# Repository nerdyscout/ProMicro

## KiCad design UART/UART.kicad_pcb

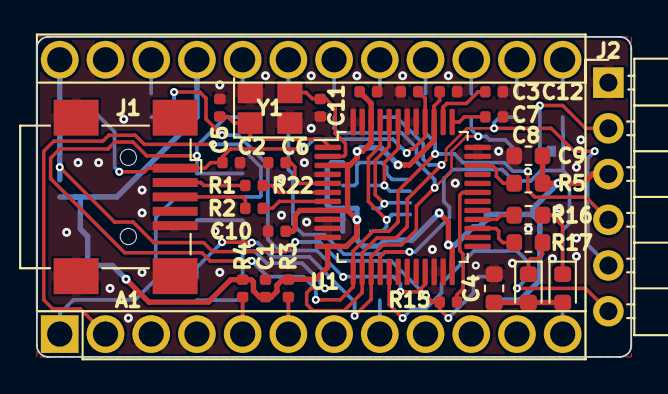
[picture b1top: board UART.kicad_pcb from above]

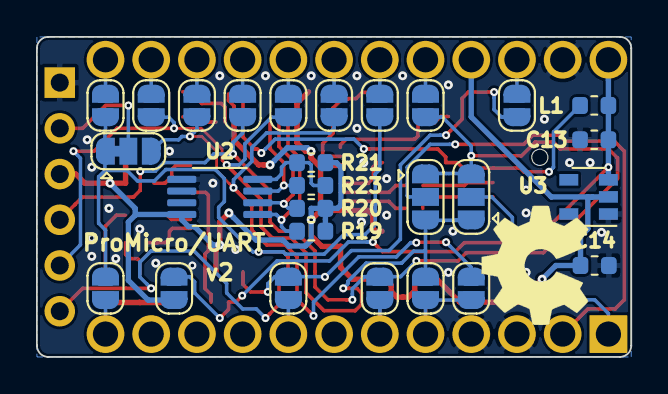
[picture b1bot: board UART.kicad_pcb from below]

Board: 4 copper layers, 33.0 x 17.8 mm, 56 parts (28 on the bottom side), 45 nets.

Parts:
A1: Sparkfun_Pro_Micro_3V3; Sparkfun_Pro_Micro
C1, C3, C7, C8, C10, C11, C12: 100n; C_0402_1005Metric
C2: 4.7µ; C_0402_1005Metric
C4: 10µ; C_0603_1608Metric
C5, C6: 27p; C_0402_1005Metric
C9: 4.7µ; R_0603_1608Metric
C13, C14: 1µ; C_0603_1608Metric
D1: TX; LED_0603_1608Metric
D2: RX; LED_0603_1608Metric
J1: USB_B_Mini; USB_Mini-B_Wuerth_65100516121_Horizontal
J2: Conn_01x06; PinHeader_1x06_P2.54mm_Horizontal
JP1, JP2, JP3, JP4, JP5, JP6, JP7, JP8, JP9, JP12, JP13, JP14, JP15, JP17, JP18: Jumper_NO_Small; SolderJumper-2_P1.3mm_Open_RoundedPad1.0x1.5mm
JP10, JP11: Jumper_3_Bridged12; SolderJumper-3_P1.3mm_Open_RoundedPad1.0x1.5mm
JP16: Jumper_3_Bridged12; SolderJumper-3_P1.3mm_Bridged12_RoundedPad1.0x1.5mm
L1: 0; L_0603_1608Metric
LOGO1: Logo_Open_Hardware_Small; OSHW-Symbol_6.7x6mm_SilkScreen
R1, R2: 22; R_0402_1005Metric
R3, R4: 4k7; R_0402_1005Metric
R5: 1k; R_0603_1608Metric
R15: 39k; R_0402_1005Metric
R16, R17: 220; R_0603_1608Metric
R19, R20, R21: 10k; R_0603_1608Metric
R22: 12k; R_0402_1005Metric
R23: 2k; R_0603_1608Metric
U1: FT232H; LQFP-48_7x7mm_P0.5mm
U2: 93CxxB; MSOP-8_3x3mm_P0.65mm
U3: AZ1117-3.3; SOT-23-5
Y1: 12MHz; Crystal_SMD_3225-4Pin_3.2x2.5mm

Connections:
+3V3: A1.21, C1.1, C4.1, C9.1, C10.2, C11.2, C12.1, C14.1, D1.2, D2.2, J2.3, JP18.2, R3.2, R4.2, R5.2, R19.2, R20.2, R21.2, U1.3, U1.8, U1.12, U1.24, U1.39, U1.46, U2.8, U3.2
+5V: A1.24, C13.1, JP18.1, L1.1, R15.2, U3.3
/CIPO: A1.15, JP3.2
/COPI: A1.14, JP2.2
/CS0: A1.13, JP5.2
/CS1: A1.12, JP4.2
/EECLK: R20.1, U1.44, U2.2
/EECS: R19.1, U1.45, U2.1
/EEDAT: R23.1, U1.43, U2.3
/PWM: A1.8, JP12.2
/RXD: A1.1, JP10.2
/SCK: A1.16, JP1.2
/SCL: A1.6, JP15.2, R3.1
/SDA: A1.5, JP13.2, JP14.2, R4.1
/TCK: A1.20, JP6.2
/TDI: A1.17, JP7.2
/TDO: A1.18, JP8.2
/TMS: A1.19, JP9.2
/TXD: A1.2, JP11.2
/~RST: A1.22, JP17.2
ACBUS0: JP12.1, JP17.1, U1.21
ADBUS0: J2.4, JP1.1, JP6.1, JP10.3, JP11.1, JP15.1, U1.13
ADBUS1: J2.5, JP2.1, JP7.1, JP10.1, JP11.3, JP13.1, U1.14
ADBUS2: JP3.1, JP8.1, JP14.1, JP16.3, U1.15
ADBUS3: JP4.1, JP5.1, JP9.1, JP16.1, U1.16
ADBUS4: J2.6, U1.17
GND: A1.3, A1.4, A1.23, C1.2, C2.2, C3.2, C4.2, C5.2, C6.2, C7.2, C8.2, C9.2, C10.1, C11.1, C12.2, C13.2, C14.2, J1.5, J1.6, J2.1, R22.2, U1.4, U1.9, U1.10, U1.11, U1.22, U1.23, U1.35, U1.36, U1.41, U1.42, U1.47, U1.48, U2.5, U3.1, Y1.2, Y1.4
unnamed: C2.1, C3.1, J1.1, L1.2, U1.40
unnamed: C5.1, U1.1, Y1.1
unnamed: C6.1, U1.2, Y1.3
unnamed: C7.1, U1.38
unnamed: C8.1, U1.37
unnamed: D1.1, R16.2
unnamed: D2.1, R17.2
unnamed: J1.2, R1.2
unnamed: J1.3, R2.2
unnamed: J2.2, JP16.2
unnamed: R1.1, U1.6
unnamed: R2.1, U1.7
unnamed: R5.1, U1.34
unnamed: R21.1, R23.2, U2.4
unnamed: R22.1, U1.5
PWRSAV: R15.1, U1.31
RXLED: R17.1, U1.27
TXLED: R16.1, U1.28

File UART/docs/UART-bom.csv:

References;Description;Part;Value;Qty;lcsc#;mpn
A1;;Sparkfun_Pro_Micro;Sparkfun_Pro_Micro_3V3;1;;
C5 C6;Unpolarized capacitor;C;27p;2;C19702;0402CG270J500NTN
C1 C3 C7 C8 C10 C11 C12;Unpolarized capacitor;C;100n;7;C1525;CL05B104KO5NNNC
C13 C14;Unpolarized capacitor;C;1µ;2;C15849;CL10A105KB8NNNC
C2;Unpolarized capacitor;C;4.7µ;1;C23733;CL05A475MP5NRNC
C9;Unpolarized capacitor;C;4.7µ;1;C19666;CL10A475KO8NNNC
C4;Unpolarized capacitor;C;10µ;1;C15525;CL10A106KP8NNNC
D2;Light emitting diode;LED;RX;1;C72043;19-217/GHC-YR1S2/3T
D1;Light emitting diode;LED;TX;1;C72043;19-217/GHC-YR1S2/3T
J2;Generic connector, single row, 01x06, script generated (kicad-library-utils/schlib/autogen/connector/);Conn_01x06;Conn_01x06;1;;
J1;USB Mini Type B connector;USB_B_Mini;USB_B_Mini;1;;
L1;Inductor, small symbol;L_Small;0;1;;
R1 R2;Resistor;R;22;2;C25092;0402WGF220JTCE
R16 R17;Resistor;R;220;2;C22962;0603WAF2200T5E
R5;Resistor;R;1k;1;C21190;0603WAF1001T5E
R23;Resistor;R;2k;1;C22975;0603WAF2001T5E
R3 R4;Resistor;R;4k7;2;C25900;0402WGF4701TCE
R19 R20 R21;Resistor;R;10k;3;C25804;0603WAF1002T5E
R22;Resistor;R;12k;1;C25752;0402WGF1202TCE
R15;Resistor;R;39k;1;C25783;0402WGF3902TCE
U2;Serial EEPROM, 93 Series, 5.0V, DIP-8/SOIC-8;93CxxB;93CxxB;1;;
U3;1A 20V Fixed LDO Linear Regulator, 3.3V, SOT-89/SOT-223/TO-220/TO-252/TO-263;AZ1117-3.3;AZ1117-3.3;1;;
U1;Hi Speed Single Channel USB UART/FIFO, LQFP/QFN-48;FT232H;FT232H;1;C51997;FT232HL
Y1;Four pin crystal, GND on pins 2 and 4, small symbol;Crystal_GND24_Small;12MHz;1;;

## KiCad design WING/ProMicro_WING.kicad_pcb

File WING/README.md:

# ProMicro_WING

## Documentation 
All files can be found on [Github](https://github.com/nerdyscout/ProMicro/tree/master/WING).

### Schematic

### BoM
  * [interactiveHTMLBoM](https://nerdyscout.github.io/ProMicro/WING/docs/bom/WING-ibom.html)
  * [octopart](docs/bom/WING-bom_octopart.csv)

## Hardware 
### Layout

### Gerbers
can be found within the Github [repository](gerbers).

## external
### Links
  * [hackaday.io](https://hackaday.io/project/171898-promicro)

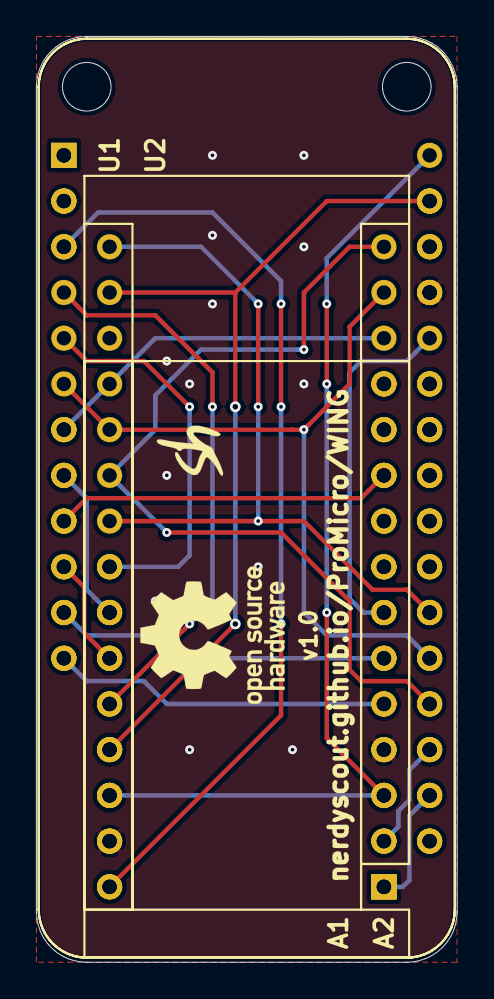
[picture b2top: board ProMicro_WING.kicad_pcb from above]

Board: 2 copper layers, 23.4 x 51.4 mm, 8 parts (0 on the bottom side), 19 nets.

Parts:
A1: Sparkfun_Pro_Micro_3V3; Sparkfun_Pro_Micro
A2: Arduino_Nano_v3.x; Arduino_Nano_mod
LOGO1: Logo_Open_Hardware_Small; OSHW-Logo_7.5x8mm_SilkScreen
TP1, TP2: TestPoint; MountingHole_2.7mm
TP3: initials
U1: Adafruit_HUZZAH32_ESP32_Feather; Adafruit_Feather_mod2
U2: Adafruit_Feather_HUZZAH_ESP8266; Adafruit_Feather

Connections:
+3V3: A1.21, A2.17, A2.27, U1.27, U2.27
+5V: A1.24, U1.3, U2.3
A0: A1.17, U1.5
A1: A1.18, U1.8, U2.8
A2: A1.19, U1.10, U2.10
A3: A1.20, U1.4
D0: A1.2, U1.15, U2.15
D1: A1.1, U1.14, U2.14
D2: A1.5, U1.12, U2.12
D3: A1.6, U1.11, U2.11
D4: A1.7, U2.24
D7: A1.10, U1.9, U2.9
D10: A1.13, U1.7, U2.7
D14: A1.15, U1.16, U2.16
D15: A1.16, U1.18, U2.18
D16: A1.14, U1.6, U1.17, U2.17
EN: U1.2, U2.2
GND: A1.4, A1.23, A2.4, A2.29, U1.25, U2.25
Reset: A1.3, A1.22, A2.3, A2.28, U2.28

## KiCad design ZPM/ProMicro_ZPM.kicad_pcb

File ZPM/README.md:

# ProMicro_ZPM 
This module can be mounted to an [Arduino Pro Mini](https://www.sparkfun.com/products/11113), [Arduino Nano](https://store.arduino.cc/arduino-nano), [Sparkfun Pro Micro](https://www.sparkfun.com/products/12587), or any other pincompatible MCU running with 3.3V.

## Documentation
All files can be found on [Github](https://github.com/nerdyscout/ProMicro/tree/master/ZPM).

### Schematic

### BoM
  * [interactiveHTMLBoM](https://nerdyscout.github.io/ProMicro/ZPM/docs/bom/ZPM-ibom.html)
  * [octopart](docs/bom/ZPM-bom_octopart.csv)

## Hardware 
### Layout

## Gerbers
can be found within the Github [repository](gerbers).

## external
### Links
  * [hackaday.io](https://hackaday.io/project/171898-promicro)

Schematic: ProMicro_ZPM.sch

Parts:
A1: Sparkfun_Pro_Micro_3V3; Sparkfun_Pro_Micro
C1: 10µF; CP_Elec_4x3
C2: 1µ; C_0603_1608Metric
C3, C4: 4.7µ; C_0603_1608Metric
J1: Screw_Terminal_01x05; TerminalBlock_TE_282834-5_1x05_P2.54mm_Horizontal
J3: JST; JST_PH_S2B-PH-SM4-TB_1x02-1MP_P2.00mm_Horizontal
JP2, JP3: SolderJumper_3_Bridged12; SolderJumper-3_P1.3mm_Bridged12_RoundedPad1.0x1.5mm
JP4: SolderJumper_2_Open; SolderJumper-2_P1.3mm_Open_RoundedPad1.0x1.5mm
L1: CDRH2D18_HPNP-100C; HPNP-100NC
LOGO1: Logo_Open_Hardware_Small; OSHW-Symbol_6.7x6mm_SilkScreen
Q1: BC847; SOT-23
R1: 2k; R_0603_1608Metric
TP1: TestPoint; TestPoint_Pad_D2.5mm
U1: LTC3588EDD-1PBF; MSOP-10-1EP_3x3mm_P0.5mm_EP1.68x1.88mm_ThermalVias
U2: MCP73831-2-OT; SOT-23-5

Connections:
+3V3: A1.21, C1.1, J1.3, L1.1, U1.6
/D0: JP2.2 (C), U1.9
/D1: JP3.2 (C), U1.8
/Vin2: C4.1, JP2.3 (B), JP3.1 (A), U1.7
GND: A1.4, A1.23, C1.2, C3.2, C4.2, J1.1, J3.1, JP2.1 (A), JP3.3 (B), Q1.2 (E), R1.2, U1.11, U2.2 (VSS)
unnamed: C2.1, U1.3
unnamed: J1.4, U1.2
unnamed: J1.5, U1.1
unnamed: JP4.2 (B), Q1.1 (B), U1.10
unnamed: L1.2, U1.5
unnamed: R1.1, U2.5 (PROG)
Reset: A1.22, JP4.1 (A), Q1.3 (C)
VBAT: C2.2, C3.1, J1.2, J3.2, TP1.1, U1.4, U2.3 (VBAT)
VCC: A1.24, U2.4 (VDD)

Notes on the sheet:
default Vout = 3.3V

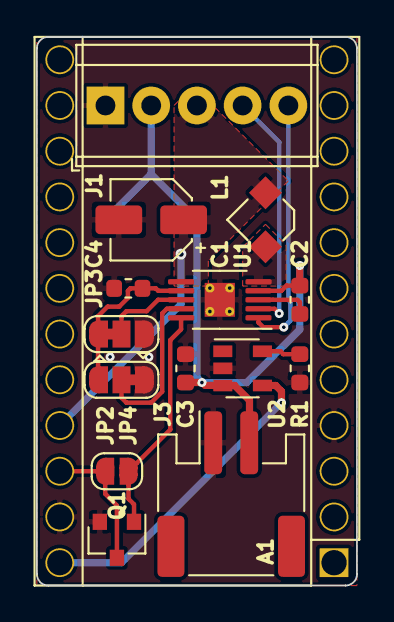
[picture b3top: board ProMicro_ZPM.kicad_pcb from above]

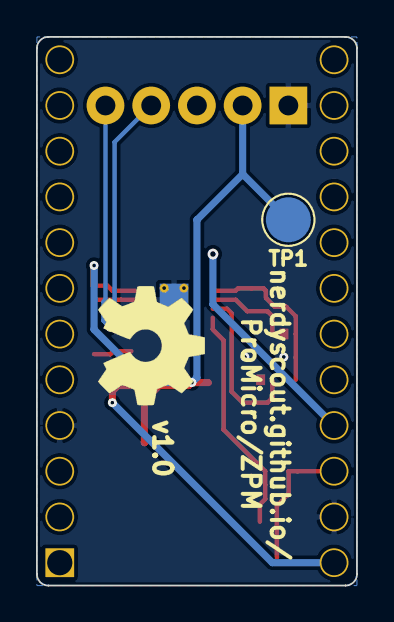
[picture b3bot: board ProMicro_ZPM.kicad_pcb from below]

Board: 2 copper layers, 17.8 x 30.5 mm, 17 parts (2 on the bottom side), 14 nets.

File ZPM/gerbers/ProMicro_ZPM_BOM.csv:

Component;Description;Part;References;Value;Footprint;Quantity Per PCB;Datasheet
1;Unpolarized capacitor;C;C2;1µ;C_0603_1608Metric;1;~
2;Unpolarized capacitor;C;C3 C4;4.7µ;C_0603_1608Metric;2;~
3;Polarized capacitor;CP;C1;10µF;CP_Elec_4x3;1;~
4;Generic connector, single row, 01x02, script generated (kicad-library-utils/schlib/autogen/connector/);Conn_01x02;J3;JST;JST_PH_S2B-PH-SM4-TB_1x02-1MP_P2.00mm_Horizontal;1;~
5;Generic screw terminal, single row, 01x05, script generated (kicad-library-utils/schlib/autogen/connector/);Screw_Terminal_01x05;J1;Screw_Terminal_01x05;TerminalBlock_TE_282834-5_1x05_P2.54mm_Horizontal;1;~
6;0.1A Ic, 45V Vce, NPN Transistor, SOT-23;BC847;Q1;BC847;SOT-23;1;http://www.infineon.com/dgdl/Infineon-BC847SERIES_BC848SERIE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
7;Resistor;R;R1;2k;R_0603_1608Metric;1;~
8;Single cell, Li-Ion/Li-Po charge management controller, 4.20V, Tri-State Status Output, in SOT23-5 package;MCP73831-2-OT;U2;MCP73831-2-OT;SOT-23-5;1;http://ww1.microchip.com/downloads/en/DeviceDoc/20001984g.pdf

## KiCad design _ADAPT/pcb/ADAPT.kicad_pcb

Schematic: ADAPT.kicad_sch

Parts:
A1: Arduino_UNO_R3
A2, A4, A5: Sparkfun_Pro_Micro; ProMicro
A3: Adafruit_Feather_Generic; Adafruit_Feather
J1, J2, J3: VBAT; PinHeader_1x01_P2.54mm_Vertical
J4, J5: Conn_01x02; PinHeader_1x02_P2.54mm_Vertical
JP1, JP2, JP4, JP6: SolderJumper_2_Open; SolderJumper-2_P1.3mm_Open_RoundedPad1.0x1.5mm
JP3, JP5: SolderJumper_3_Open; SolderJumper-3_P1.3mm_Open_RoundedPad1.0x1.5mm
LOGO1: Logo_Open_Hardware_Small; OSHW-Symbol_6.7x6mm_SilkScreen

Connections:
+3V3: A1.4 (3V3), A2.21, A3.2 (3V3), A4.21, A5.21, JP3.1 (A)
+5V: A1.5 (+5V), A2.24, A3.26 (USB), A4.24, A5.24
A0: A1.9 (A0), A2.17, A3.5 (A0), A4.17, A5.17, JP5.2 (C)
A1: A1.10 (A1), A2.18, A3.6 (A1), A4.18, A5.18
A2: A1.11 (A2), A2.19, A3.7 (A2), A4.19, A5.19
A3: A1.12 (A3), A2.20, A3.8 (A3), A4.20, A5.20
AREF: A1.30 (AREF), A3.3 (AREF)
BTN: A2.9, A4.9, A5.9, JP5.3 (B)
CIPO: A1.27 (D12), A2.15, A3.13 (MISO), A4.15, A5.15
COPI: A1.26 (D11), A2.14, A3.12 (MOSI), A4.14, A5.14
CS0: A1.25 (D10), A2.13, A3.22 (D3), A4.13, A5.13
CS1: A1.24 (D9), A2.12, A3.23 (D4), A4.12, A5.12
D8: A1.23 (D8), A2.11, A3.25 (D6), A4.11, A5.11
GND: A1.6 (GND), A1.7 (GND), A1.29 (GND), A2.3, A2.4, A2.23, A3.4 (GND), A4.3, A4.4, A4.23, A5.3, A5.4, A5.23, JP3.3 (B)
INT: A1.17 (D2), A2.10, A3.21 (D2), A4.10, A5.10
unnamed: A3.9 (A4), JP6.1 (A)
unnamed: A3.10 (A5), JP4.1 (A)
unnamed: A3.19 (D0), JP1.2 (B)
unnamed: A3.20 (D1), JP2.2 (B)
unnamed: J1.1, J2.1, J3.1
PWM: A1.20 (D5), A2.8, A3.24 (D5), A4.8, A5.8
RXD: A1.16 (D1/TX), A2.1, A3.14 (RX), A4.1, A5.1, JP1.1 (A)
SCK: A1.28 (D13), A2.16, A3.11 (SCK), A4.16, A5.16
SCL: A1.13 (SDA/A4), A1.32 (SCL/A5), A2.6, A3.18 (SCL), A4.6, A5.6, J4.2, J5.2, JP6.2 (B)
SDA: A1.14 (SCL/A5), A1.31 (SDA/A4), A2.5, A3.17 (SDA), A4.5, A5.5, J4.1, J5.1, JP4.2 (B)
SPARE: A3.16 (SPARE), JP3.2 (C)
STAT: A1.19 (D4), A2.7, A4.7, A5.7, JP5.1 (A)
TXD: A1.15 (D0/RX), A2.2, A3.15 (TX), A4.2, A5.2, JP2.1 (A)
~RST: A1.3 (~RESET), A2.22, A3.1 (~RESET), A4.22, A5.22

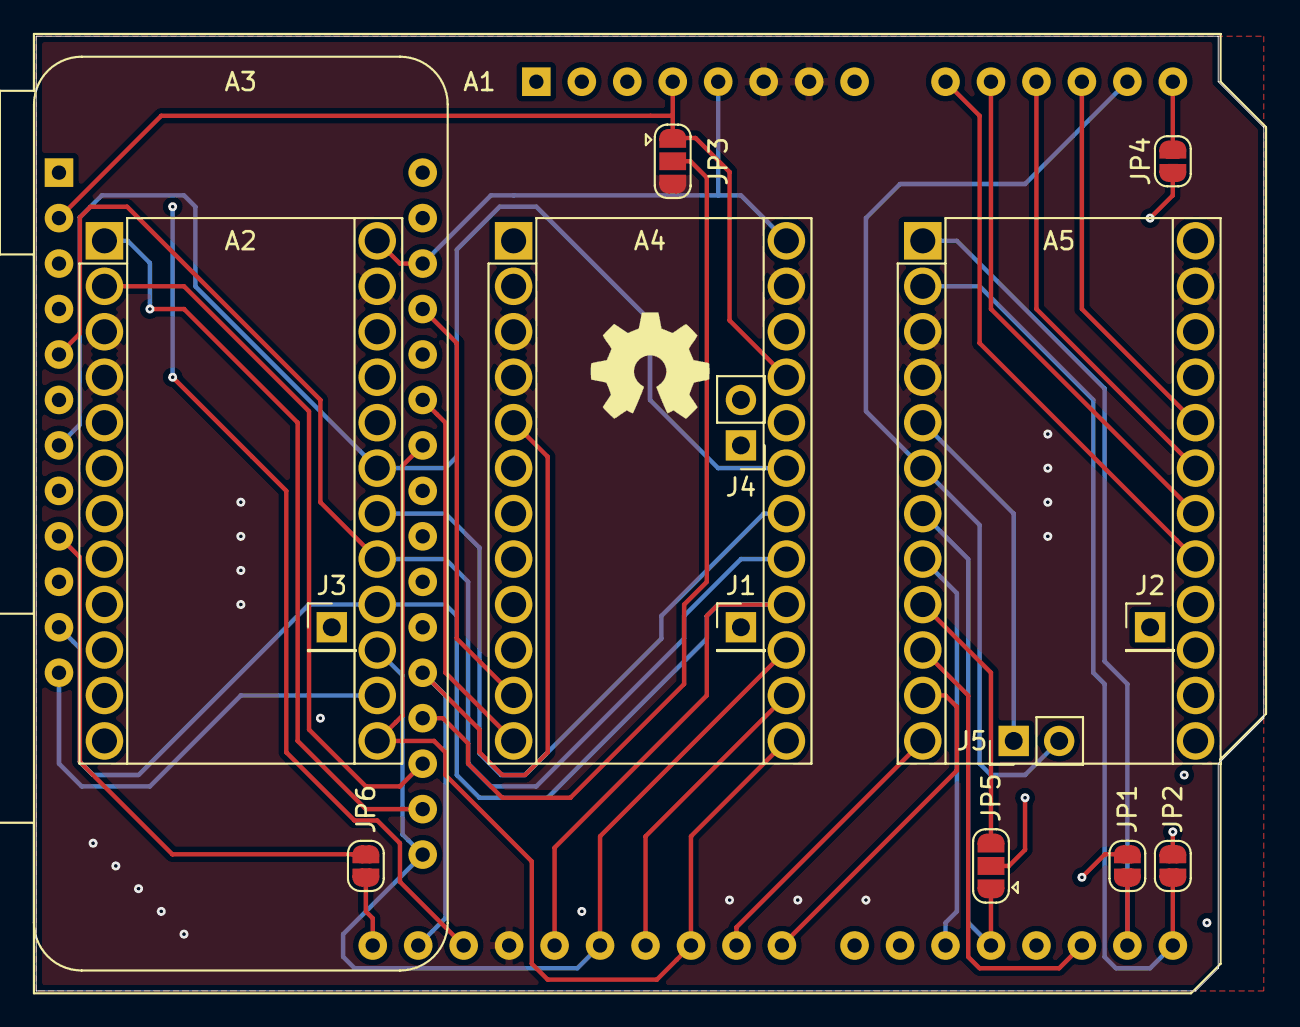
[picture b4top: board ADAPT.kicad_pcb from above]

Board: 4 copper layers, 68.6 x 53.3 mm, 17 parts (0 on the bottom side), 29 nets.

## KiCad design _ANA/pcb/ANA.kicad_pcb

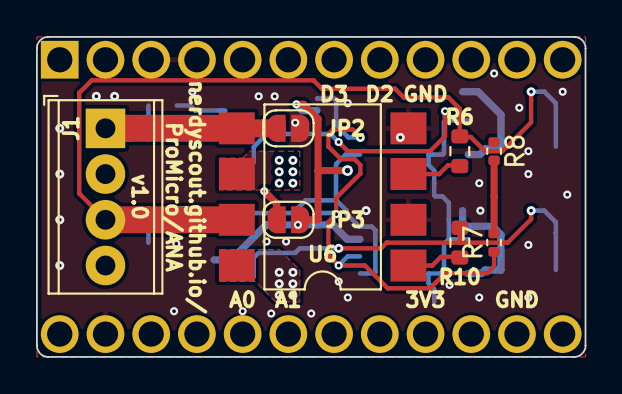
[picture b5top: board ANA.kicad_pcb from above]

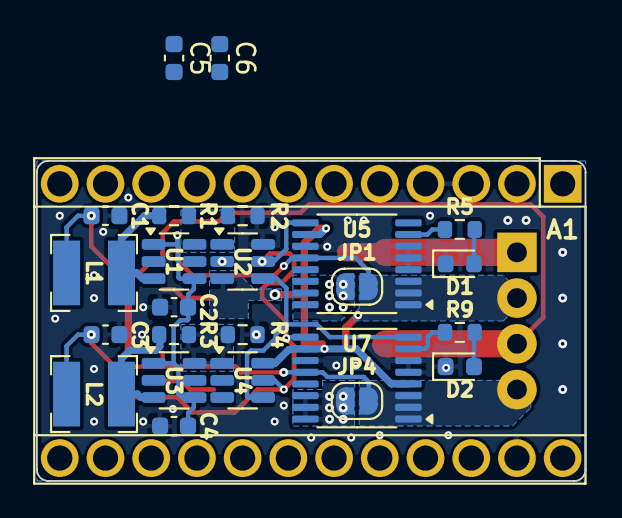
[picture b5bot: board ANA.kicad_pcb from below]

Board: 2 copper layers, 30.5 x 17.8 mm, 34 parts (25 on the bottom side), 20 nets.

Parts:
A1: Sparkfun_Pro_Micro
C1, C3: 10µ; C_0603_1608Metric
C2, C4: 4.7µ; C_0603_1608Metric
C5, C6: 100n; C_0603_1608Metric
D1, D2: LED; LED_0603_1608Metric
J1: Conn_01x04; TerminalBlock_Phoenix_MPT-0,5-4-2.54_1x04_P2.54mm_Horizontal
JP1, JP2, JP3, JP4: Jumper_NO_Small; SolderJumper-2_P1.3mm_Open_RoundedPad1.0x1.5mm
L1, L2: 2.2µ; L_Bourns-SRN4018
LOGO1: Logo_Open_Hardware_Small; OSHW-Symbol_6.7x6mm_SilkScreen
R1, R3: 200k; R_0603_1608Metric
R2, R4: 47k; R_0603_1608Metric
R5, R6, R9, R10: 220; R_0603_1608Metric
R7, R8: 4k7; R_0402_1005Metric
U1, U3: TLV62569DDC; SOT-23-6
U2, U4: MCP4725xxx-xCH; SOT-23-6
U5, U7: INA260; TSSOP-16_4.4x5mm_P0.65mm
U6: LTV-827S; SMDIP-8_W9.53mm

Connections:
+3V3: A1.21, C5.1, C6.1, JP3.2, R7.2, R8.2, U2.3, U4.3, U4.6, U5.10, U7.4, U7.10
A0: A1.17, C1.1, J1.3, L1.1, R6.2, U6.5
A1: A1.18, C3.1, J1.4, JP4.1, L2.1, R10.2, U7.1, U7.2, U7.3, U7.12
GND: A1.3, A1.4, A1.23, C1.2, C2.2, C3.2, C4.2, C5.2, C6.2, D1.1, D2.1, JP2.2, R2.1, R4.1, U1.2, U2.2, U2.6, U3.2, U4.2, U5.4, U5.5, U5.6, U5.11, U6.2, U6.4, U7.5, U7.6, U7.11
unnamed: C2.1, C4.1, J1.2, JP1.1, JP3.1, U1.1, U1.4, U3.1, U3.4, U5.1, U5.2, U5.3, U5.12
unnamed: D1.2, R5.1
unnamed: D2.2, R9.1
unnamed: J1.1, JP2.1, U6.7
unnamed: JP1.2, U5.14, U5.15, U5.16, U6.8
unnamed: JP4.2, U6.6, U7.14, U7.15, U7.16
unnamed: L1.2, R1.2, U1.3
unnamed: L2.2, R3.2, U3.3
unnamed: R1.1, R2.2, U1.6, U2.1
unnamed: R3.1, R4.2, U3.6, U4.1
unnamed: R5.2, U5.7
unnamed: R6.1, U6.1
unnamed: R9.2, U7.7
unnamed: R10.1, U6.3
SCL: A1.6, R7.1, U2.5, U4.5, U5.9, U7.9
SDA: A1.5, R8.1, U2.4, U4.4, U5.8, U7.8

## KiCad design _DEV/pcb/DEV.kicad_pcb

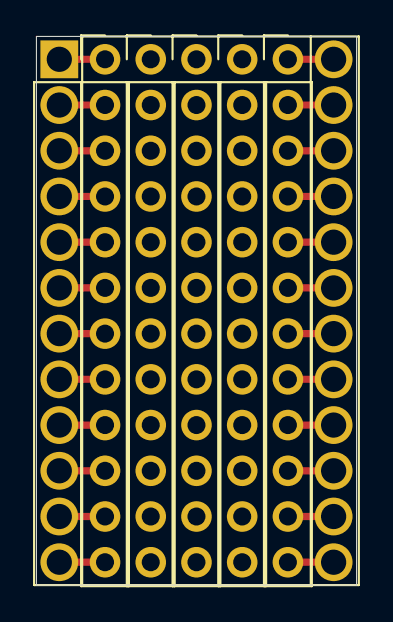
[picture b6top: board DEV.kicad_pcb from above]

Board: 2 copper layers, 17.8 x 30.5 mm, 6 parts (0 on the bottom side), 22 nets.

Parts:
A1: Sparkfun_Pro_Micro; ProMicro
J1, J2, J3, J4, J5: Conn_01x12; PinHeader_1x12_P2.54mm_Vertical

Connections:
+3V3: A1.21, J2.4
+5V: A1.24, J2.1
BTN: A1.9, J1.9
CIPO: A1.15, J2.10
COPI: A1.14, J2.11
CS0: A1.13, J2.12
CS1: A1.12, J1.12
D8: A1.11, J1.11
GND: A1.3, A1.4, A1.23, J1.3, J1.4, J2.2
INT: A1.10, J1.10
PWM: A1.8, J1.8
RXD: A1.1, J1.1
SCK: A1.16, J2.9
SCL: A1.6, J1.6
SDA: A1.5, J1.5
STAT: A1.7, J1.7
TCK: A1.20, J2.5
TDI: A1.17, J2.8
TDO: A1.18, J2.7
TMS: A1.19, J2.6
TXD: A1.2, J1.2
~RST: A1.22, J2.3

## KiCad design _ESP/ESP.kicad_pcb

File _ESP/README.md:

# ProMicro_ESP 
This module can be mounted to an [Arduino Pro Mini](https://www.sparkfun.com/products/11113), [Arduino Nano](https://store.arduino.cc/arduino-nano), [Sparkfun Pro Micro](https://www.sparkfun.com/products/12587), or any other pincompatible MCU running with 3.3V.

## Documentation 
All files can be found on [Github](https://github.com/nerdyscout/ProMicro/tree/master/ESP).

### Schematic

### BoM
  * [interactiveHTMLBoM](https://nerdyscout.github.io/ProMicro/ESP/docs/bom/ESP-ibom.html)
  * [octopart](pcb/docs/bom/ESP-bom_octopart.csv)

## Hardware 
### Layout

### Gerbers
can be found within the Github [repository](pcb/gerbers).

## Code  (unless otherwise stated)
 * [blink](examples/blink/blink.ino)

## external
### Links
  * [hackaday.io](https://hackaday.io/project/171898-promicro)

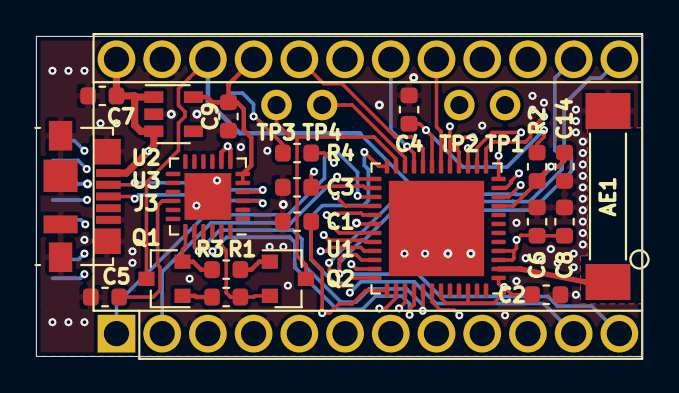
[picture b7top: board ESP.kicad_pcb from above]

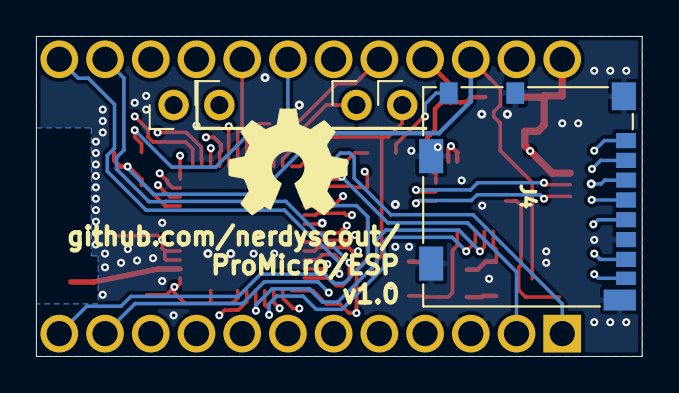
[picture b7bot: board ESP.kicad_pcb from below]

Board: 4 copper layers, 33.7 x 17.8 mm, 28 parts (6 on the bottom side), 44 nets.

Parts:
A1: Sparkfun_Pro_Micro; ProMicro
AE1: Antenna_Chip; SMD_ANT9520
C1, C2, C7, C14: 1µ; C_0603_1608Metric
C3, C9: 0.1n; C_0603_1608Metric
C4, C6: 100n; C_0603_1608Metric
C5: DNP; C_0603_1608Metric
C8: 10n; C_0603_1608Metric
J3: USB_B_Micro; USB_Micro-B_Molex_47346-0001
J4: Micro_SD_Card_Det; microSD_HC_Molex_104031-0811
LOGO1: Logo_Open_Hardware_Small; OSHW-Symbol_6.7x6mm_SilkScreen
Q1, Q2: mmbt2222; SOT-23
R1, R2, R3, R4: 10k; R_0603_1608Metric
TP1: GPIO21; PinHeader_1x01_P2.54mm_Vertical
TP2: GPIO22; PinHeader_1x01_P2.54mm_Vertical
TP3: GPIO0; PinHeader_1x01_P2.54mm_Vertical
TP4: GPIO2; PinHeader_1x01_P2.54mm_Vertical
U1: ESP32-PICO-D4; QFN-48-1EP_7x7mm_P0.5mm_EP5.3x5.3mm
U2: AP2112K-3.3; SOT-23-5
U3: CP2104; QFN-24-1EP_4x4mm_P0.5mm_EP2.6x2.6mm

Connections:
+3V3: A1.21, C1.1, C2.1, C4.1, C6.1, C8.1, C9.1, R2.1, U1.1, U1.3, U1.4, U1.19, U1.37, U1.43, U1.46, U2.5, U3.5, U3.6
+5V: A1.24, C7.1, J3.1, U2.1, U2.3, U3.7, U3.8
/CLK: J4.5, U1.31
/CMD: J4.3, U1.30
/D0: J4.7, U1.32
/D1: J4.8, U1.33
/D2: J4.1, U1.28
/D3: J4.2, U1.29
/D+: J3.3, U3.3
/D-: J3.2, U3.4
/DTR: Q2.2, R1.2, U3.23
/GPIO0: Q2.3, TP3.1, U1.23
/GPIO2: TP4.1, U1.22
/RTS: Q1.2, R3.2, U3.19
/VDDSDIO: C3.1, J4.4, U1.26
BTN: A1.9, R4.1, U1.14
CIPO: A1.15, U1.38
COPI: A1.14, U1.36
CS0: A1.13, U1.34
CS1: A1.12, U1.24
D8: A1.11, U1.16
GND: A1.3, A1.4, A1.23, AE1.2, C1.2, C2.2, C3.2, C4.2, C5.2, C6.2, C7.2, C8.2, C9.2, C14.2, J3.5, J3.6, J4.6, J4.9, J4.11, U1.49, U2.2, U3.2, U3.25
INT: A1.10, U1.13
unnamed: AE1.1, U1.2
unnamed: C5.1, U3.16
unnamed: J4.10, R4.2
unnamed: Q1.1, R1.1
unnamed: Q2.1, R3.1
unnamed: TP1.1, U1.42
unnamed: TP2.1, U1.39
PWM: A1.8, U1.12
RXD: U1.40, U3.21
RXD2: A1.2, U1.25
SCK: A1.16, U1.35
SCL: A1.6, U1.10
SDA: A1.5, U1.11
STAT: A1.7, U1.15
TCK: A1.20, U1.20
TDI: A1.17, U1.18
TDO: A1.18, U1.21
TMS: A1.19, U1.17
TXD: U1.41, U3.20
TXD2: A1.1, U1.27
~RST: A1.22, C14.1, Q1.3, R2.2, U1.9

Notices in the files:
WING/README.md:
Documentation [![CC BY-SA](../img/ccbysa.png)](docs/LICENSE.TXT):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
_ESP/README.md:
Documentation [![CC BY-SA](../img/ccbysa.png)](pcb/docs/LICENSE.TXT):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
